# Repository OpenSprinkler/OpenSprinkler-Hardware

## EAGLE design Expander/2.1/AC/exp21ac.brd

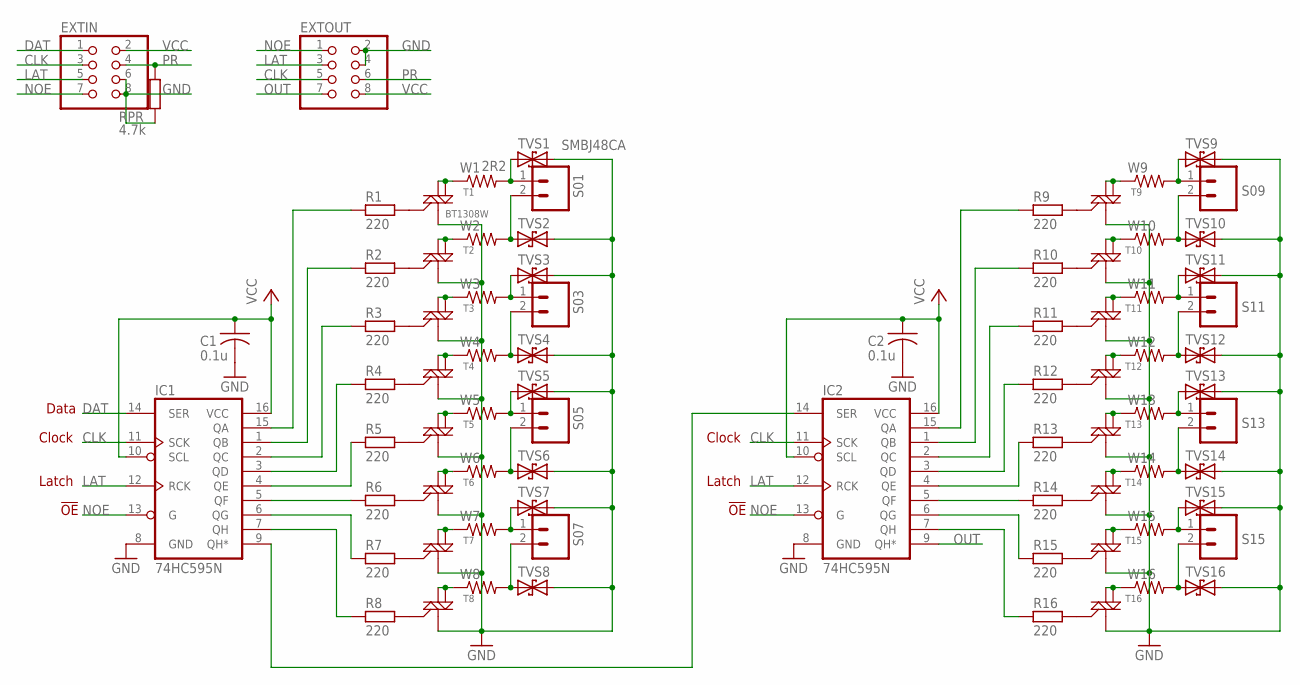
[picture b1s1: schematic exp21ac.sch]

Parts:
C1, C2: 0.1u; C0603K
EXTIN: PINHD-2X4/90; 2X04/90
EXTOUT: PINHD-2X4/90; 2X04/90
IC1, IC2: 74HC595N; SO16
R1, R2, R3, R4, R5, R6, R7, R8, R9, R10, R11, R12, R13, R14, R15, R16: 220; R0603
RPR: 4.7k; R0603
S01, S03, S05, S07, S09, S11, S13, S15: M025MM-X; SCREWTERMINAL-5MM-2-X
T1: BT1308W; SOT223
T2, T3, T4, T5, T6, T7, T8: MAC97SOT223; SOT223
T9, T10, T11, T12, T13, T14, T15, T16: MAC97; SOT223
TVS1: SMBJ48CA; SMB
TVS2, TVS3, TVS4, TVS5, TVS6, TVS7, TVS8, TVS9, TVS10, TVS11, TVS12, TVS13, TVS14, TVS15, TVS16: TVSSMB; SMB
W1: 2R2; R2512
W2, W3, W4, W5, W6, W7, W8, W9, W10, W11, W12, W13, W14, W15, W16: R-US_R2512; R2512

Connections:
CLK: EXTIN.3, EXTOUT.5, IC1.11 (SCK), IC2.11 (SCK)
DAT: EXTIN.1, IC1.14 (SER)
GND: C1.2, C2.2, EXTIN.6, EXTIN.8, EXTOUT.2, EXTOUT.4, IC1.8 (GND), IC2.8 (GND), RPR.1, T1.1 (M1), T2.1 (M1), T3.1 (M1), T4.1 (M1), T5.1 (M1), T6.1 (M1), T7.1 (M1), T8.1 (M1), T9.1 (M1), T10.1 (M1), T11.1 (M1), T12.1 (M1), T13.1 (M1), T14.1 (M1), T15.1 (M1), T16.1 (M1), TVS1.C (2), TVS2.C (2), TVS3.C (2), TVS4.C (2), TVS5.C (2), TVS6.C (2), TVS7.C (2), TVS8.C (2), TVS9.C (2), TVS10.C (2), TVS11.C (2), TVS12.C (2), TVS13.C (2), TVS14.C (2), TVS15.C (2), TVS16.C (2)
LAT: EXTIN.5, EXTOUT.3, IC1.12 (RCK), IC2.12 (RCK)
unnamed: S01.1, TVS1.A (1), W1.2
unnamed: S03.1, TVS3.A (1), W3.2
unnamed: S05.1, TVS5.A (1), W5.2
unnamed: IC1.5 (QF), R6.2
unnamed: IC1.6 (QG), R7.2
unnamed: S07.1, TVS7.A (1), W7.2
unnamed: IC1.7 (QH), R8.2
unnamed: R1.1, T1.3 (G)
unnamed: R2.1, T2.3 (G)
unnamed: IC1.4 (QE), R5.2
unnamed: IC1.3 (QD), R4.2
unnamed: IC1.2 (QC), R3.2
unnamed: IC1.1 (QB), R2.2
unnamed: IC1.15 (QA), R1.2
unnamed: R3.1, T3.3 (G)
unnamed: R4.1, T4.3 (G)
unnamed: S01.2, TVS2.A (1), W2.2
unnamed: R5.1, T5.3 (G)
unnamed: R6.1, T6.3 (G)
unnamed: S03.2, TVS4.A (1), W4.2
unnamed: R7.1, T7.3 (G)
unnamed: R8.1, T8.3 (G)
unnamed: S05.2, TVS6.A (1), W6.2
unnamed: IC2.5 (QF), R14.2
unnamed: S07.2, TVS8.A (1), W8.2
unnamed: IC2.6 (QG), R15.2
unnamed: IC2.7 (QH), R16.2
unnamed: IC2.4 (QE), R13.2
unnamed: IC2.3 (QD), R12.2
unnamed: IC2.2 (QC), R11.2
unnamed: IC2.1 (QB), R10.2
unnamed: IC2.15 (QA), R9.2
unnamed: S09.2, TVS10.A (1), W10.2
unnamed: S11.2, TVS12.A (1), W12.2
unnamed: S13.2, TVS14.A (1), W14.2
unnamed: S15.2, TVS16.A (1), W16.2
unnamed: S09.1, TVS9.A (1), W9.2
unnamed: S11.1, TVS11.A (1), W11.2
unnamed: S13.1, TVS13.A (1), W13.2
unnamed: S15.1, TVS15.A (1), W15.2
unnamed: R9.1, T9.3 (G)
unnamed: R10.1, T10.3 (G)
unnamed: R11.1, T11.3 (G)
unnamed: R12.1, T12.3 (G)
unnamed: R13.1, T13.3 (G)
unnamed: R14.1, T14.3 (G)
unnamed: R15.1, T15.3 (G)
unnamed: R16.1, T16.3 (G)
unnamed: IC1.9 (QH*), IC2.14 (SER)
unnamed: T1.2 (M2), T1.4 (M2-4), W1.1
unnamed: T2.2 (M2), T2.4 (M2-4), W2.1
unnamed: T3.2 (M2), T3.4 (M2-4), W3.1
unnamed: T4.2 (M2), T4.4 (M2-4), W4.1
unnamed: T5.2 (M2), T5.4 (M2-4), W5.1
unnamed: T6.2 (M2), T6.4 (M2-4), W6.1
unnamed: T7.2 (M2), T7.4 (M2-4), W7.1
unnamed: T8.2 (M2), T8.4 (M2-4), W8.1
unnamed: T9.2 (M2), T9.4 (M2-4), W9.1
unnamed: T10.2 (M2), T10.4 (M2-4), W10.1
unnamed: T11.2 (M2), T11.4 (M2-4), W11.1
unnamed: T12.2 (M2), T12.4 (M2-4), W12.1
unnamed: T13.2 (M2), T13.4 (M2-4), W13.1
unnamed: T14.2 (M2), T14.4 (M2-4), W14.1
unnamed: T15.2 (M2), T15.4 (M2-4), W15.1
unnamed: T16.2 (M2), T16.4 (M2-4), W16.1
NOE: EXTIN.7, EXTOUT.1, IC1.13 (G), IC2.13 (G)
OUT: EXTOUT.7, IC2.9 (QH*)
PR: EXTIN.4, EXTOUT.6, RPR.2
VCC: C1.1, C2.1, EXTIN.2, EXTOUT.8, IC1.10 (SCL), IC1.16 (VCC), IC2.10 (SCL), IC2.16 (VCC)

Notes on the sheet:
Data
Clock
Latch
!OE

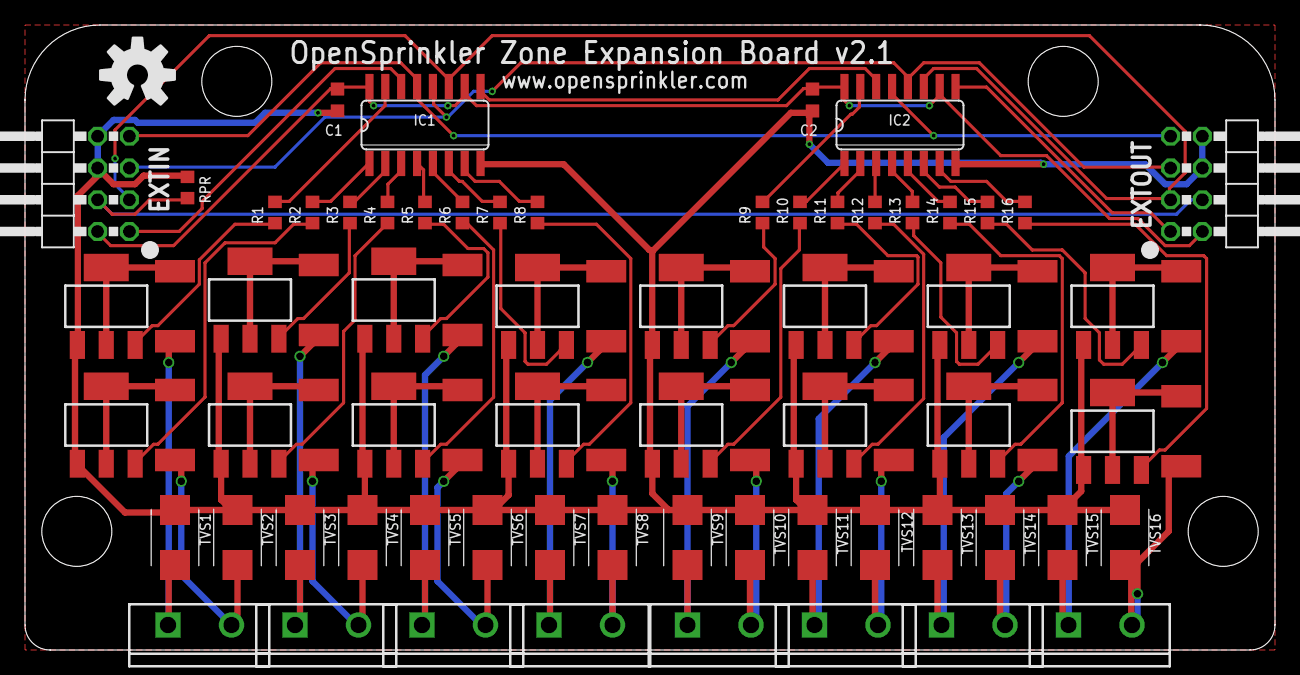
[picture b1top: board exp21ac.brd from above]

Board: 2 copper layers, 100.0 x 50.0 mm, 79 parts (0 on the bottom side), 73 nets.

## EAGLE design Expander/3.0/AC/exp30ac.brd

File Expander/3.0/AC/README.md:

- Original expander 3.0 uses PCF8575 16-channel IO expander. Due to the weak source current, PNP transistors are used per channel to provide higher source current needed to drive triac.

- Expander 3.0 revision 1 uses PCA9555 16-channel IO expander, which provides higher source current and therefore eliminates the need of PNP transistors.

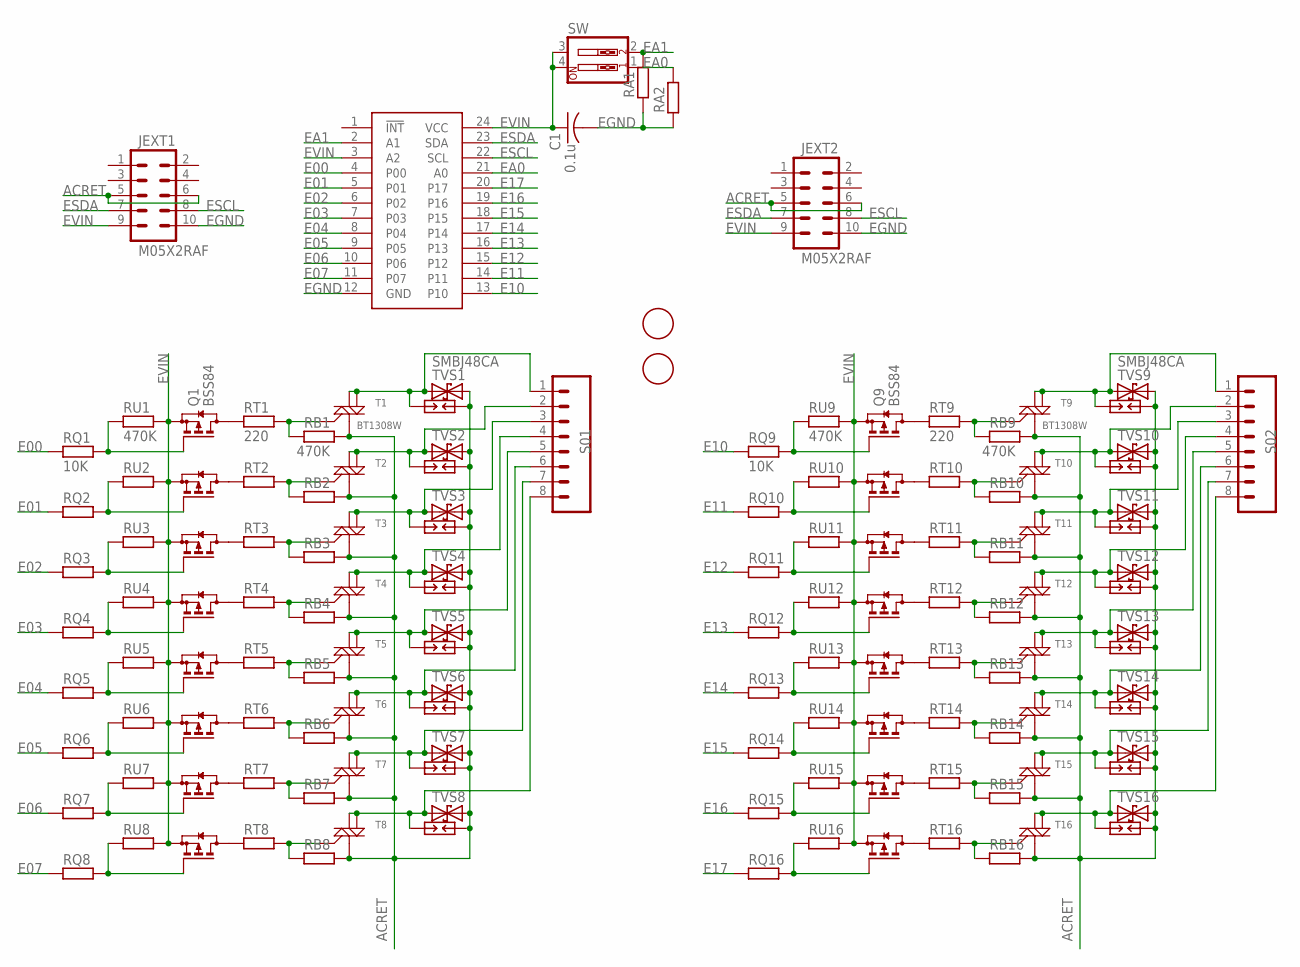
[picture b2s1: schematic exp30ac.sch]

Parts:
C1: 0.1u; C0603
JEXT1, JEXT2: M05X2RAF; 2X5-RAF
PCF8575: PCF8575; SSOP24
Q1, Q2, Q3, Q4, Q5, Q6, Q7, Q8, Q9, Q10, Q11, Q12, Q13, Q14, Q15, Q16: BSS84; SOT23
RA1, RA2: 10K; R0603
RB1, RB2, RB3, RB4, RB5, RB6, RB7, RB8, RB9, RB10, RB11, RB12, RB13, RB14, RB15, RB16: 470K; R0603
RQ1, RQ2, RQ3, RQ4, RQ5, RQ6, RQ7, RQ8, RQ9, RQ10, RQ11, RQ12, RQ13, RQ14, RQ15, RQ16: 10K; R0603
RT1, RT2, RT3, RT4, RT5, RT6, RT7, RT8, RT9, RT10, RT11, RT12, RT13, RT14, RT15, RT16: 220; R0603
RU1, RU2, RU3, RU4, RU5, RU6, RU7, RU8, RU9, RU10, RU11, RU12, RU13, RU14, RU15, RU16: 470K; R0603
S01, S02: M085MM-8; SCREWTERMINAL-5MM-8
SP1, SP2, SP3, SP4, SP5, SP6, SP7, SP8, SP9, SP10, SP11, SP12, SP13, SP14, SP15, SP16: PCB-SGAP
SW: SW_DIP-2; DIPSWITCH-02
T1, T9: BT1308W; SOT223
T2, T3, T4, T5, T6, T7, T8, T10, T11, T12, T13, T14, T15, T16: MAC97SOT223; SOT223
TVS1, TVS9: SMBJ48CA; SMB
TVS2, TVS3, TVS4, TVS5, TVS6, TVS7, TVS8, TVS10, TVS11, TVS12, TVS13, TVS14, TVS15, TVS16: TVSSMB; SMB
U$1, U$2: FIDUCIAL; FIDUCIAL_1MM

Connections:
ACRET: JEXT1.5, JEXT1.6, JEXT2.5, JEXT2.6, RB1.1, RB2.1, RB3.1, RB4.1, RB5.1, RB6.1, RB7.1, RB8.1, RB9.1, RB10.1, RB11.1, RB12.1, RB13.1, RB14.1, RB15.1, RB16.1, SP1.1, SP2.1, SP3.1, SP4.1, SP5.1, SP6.1, SP7.1, SP8.1, SP9.1, SP10.1, SP11.1, SP12.1, SP13.1, SP14.1, SP15.1, SP16.1, T1.1 (M1), T2.1 (M1), T3.1 (M1), T4.1 (M1), T5.1 (M1), T6.1 (M1), T7.1 (M1), T8.1 (M1), T9.1 (M1), T10.1 (M1), T11.1 (M1), T12.1 (M1), T13.1 (M1), T14.1 (M1), T15.1 (M1), T16.1 (M1), TVS1.C, TVS2.C, TVS3.C, TVS4.C, TVS5.C, TVS6.C, TVS7.C, TVS8.C, TVS9.C, TVS10.C, TVS11.C, TVS12.C, TVS13.C, TVS14.C, TVS15.C, TVS16.C
E00: PCF8575.4 (P00), RQ1.2
E01: PCF8575.5 (P01), RQ2.2
E02: PCF8575.6 (P02), RQ3.2
E03: PCF8575.7 (P03), RQ4.2
E04: PCF8575.8 (P04), RQ5.2
E05: PCF8575.9 (P05), RQ6.2
E06: PCF8575.10 (P06), RQ7.2
E07: PCF8575.11 (P07), RQ8.2
E10: PCF8575.13 (P10), RQ9.2
E11: PCF8575.14 (P11), RQ10.2
E12: PCF8575.15 (P12), RQ11.2
E13: PCF8575.16 (P13), RQ12.2
E14: PCF8575.17 (P14), RQ13.2
E15: PCF8575.18 (P15), RQ14.2
E16: PCF8575.19 (P16), RQ15.2
E17: PCF8575.20 (P17), RQ16.2
EA0: PCF8575.21 (A0), RA2.1, SW.1
EA1: PCF8575.2 (A1), RA1.1, SW.2
EGND: C1.2, JEXT1.10, JEXT2.10, PCF8575.12 (GND), RA1.2, RA2.2
ESCL: JEXT1.8, JEXT2.8, PCF8575.22 (SCL)
ESDA: JEXT1.7, JEXT2.7, PCF8575.23 (SDA)
EVIN: C1.1, JEXT1.9, JEXT2.9, PCF8575.3 (A2), PCF8575.24 (VCC), Q1.2 (S), Q2.2 (S), Q3.2 (S), Q4.2 (S), Q5.2 (S), Q6.2 (S), Q7.2 (S), Q8.2 (S), Q9.2 (S), Q10.2 (S), Q11.2 (S), Q12.2 (S), Q13.2 (S), Q14.2 (S), Q15.2 (S), Q16.2 (S), RU1.1, RU2.1, RU3.1, RU4.1, RU5.1, RU6.1, RU7.1, RU8.1, RU9.1, RU10.1, RU11.1, RU12.1, RU13.1, RU14.1, RU15.1, RU16.1, SW.3, SW.4
unnamed: RB9.2, RT9.1, T9.3 (G)
unnamed: Q1.3 (D), RT1.2
unnamed: Q2.3 (D), RT2.2
unnamed: Q3.3 (D), RT3.2
unnamed: Q4.3 (D), RT4.2
unnamed: Q5.3 (D), RT5.2
unnamed: Q6.3 (D), RT6.2
unnamed: RB1.2, RT1.1, T1.3 (G)
unnamed: RB2.2, RT2.1, T2.3 (G)
unnamed: Q7.3 (D), RT7.2
unnamed: Q8.3 (D), RT8.2
unnamed: Q1.1 (G), RQ1.1, RU1.2
unnamed: Q2.1 (G), RQ2.1, RU2.2
unnamed: Q3.1 (G), RQ3.1, RU3.2
unnamed: RB3.2, RT3.1, T3.3 (G)
unnamed: RB4.2, RT4.1, T4.3 (G)
unnamed: RB10.2, RT10.1, T10.3 (G)
unnamed: RB5.2, RT5.1, T5.3 (G)
unnamed: RB6.2, RT6.1, T6.3 (G)
unnamed: Q4.1 (G), RQ4.1, RU4.2
unnamed: RB7.2, RT7.1, T7.3 (G)
unnamed: RB8.2, RT8.1, T8.3 (G)
unnamed: Q5.1 (G), RQ5.1, RU5.2
unnamed: RB11.2, RT11.1, T11.3 (G)
unnamed: Q6.1 (G), RQ6.1, RU6.2
unnamed: RB12.2, RT12.1, T12.3 (G)
unnamed: RB13.2, RT13.1, T13.3 (G)
unnamed: RB14.2, RT14.1, T14.3 (G)
unnamed: RB15.2, RT15.1, T15.3 (G)
unnamed: RB16.2, RT16.1, T16.3 (G)
unnamed: Q7.1 (G), RQ7.1, RU7.2
unnamed: Q8.1 (G), RQ8.1, RU8.2
unnamed: S02.1, SP9.2, T9.2 (M2), T9.4 (M2-4), TVS9.A
unnamed: S02.2, SP10.2, T10.2 (M2), T10.4 (M2-4), TVS10.A
unnamed: S02.3, SP11.2, T11.2 (M2), T11.4 (M2-4), TVS11.A
unnamed: S02.4, SP12.2, T12.2 (M2), T12.4 (M2-4), TVS12.A
unnamed: S02.5, SP13.2, T13.2 (M2), T13.4 (M2-4), TVS13.A
unnamed: S02.6, SP14.2, T14.2 (M2), T14.4 (M2-4), TVS14.A
unnamed: S02.7, SP15.2, T15.2 (M2), T15.4 (M2-4), TVS15.A
unnamed: S02.8, SP16.2, T16.2 (M2), T16.4 (M2-4), TVS16.A
unnamed: Q9.3 (D), RT9.2
unnamed: Q10.3 (D), RT10.2
unnamed: Q11.3 (D), RT11.2
unnamed: Q12.3 (D), RT12.2
unnamed: Q13.3 (D), RT13.2
unnamed: Q14.3 (D), RT14.2
unnamed: Q15.3 (D), RT15.2
unnamed: Q16.3 (D), RT16.2
unnamed: Q9.1 (G), RQ9.1, RU9.2
unnamed: S01.1, SP1.2, T1.2 (M2), T1.4 (M2-4), TVS1.A
unnamed: S01.2, SP2.2, T2.2 (M2), T2.4 (M2-4), TVS2.A
unnamed: S01.3, SP3.2, T3.2 (M2), T3.4 (M2-4), TVS3.A
unnamed: S01.4, SP4.2, T4.2 (M2), T4.4 (M2-4), TVS4.A
unnamed: S01.5, SP5.2, T5.2 (M2), T5.4 (M2-4), TVS5.A
unnamed: S01.6, SP6.2, T6.2 (M2), T6.4 (M2-4), TVS6.A
unnamed: S01.7, SP7.2, T7.2 (M2), T7.4 (M2-4), TVS7.A
unnamed: S01.8, SP8.2, T8.2 (M2), T8.4 (M2-4), TVS8.A
unnamed: Q10.1 (G), RQ10.1, RU10.2
unnamed: Q11.1 (G), RQ11.1, RU11.2
unnamed: Q12.1 (G), RQ12.1, RU12.2
unnamed: Q13.1 (G), RQ13.1, RU13.2
unnamed: Q14.1 (G), RQ14.1, RU14.2
unnamed: Q15.1 (G), RQ15.1, RU15.2
unnamed: Q16.1 (G), RQ16.1, RU16.2

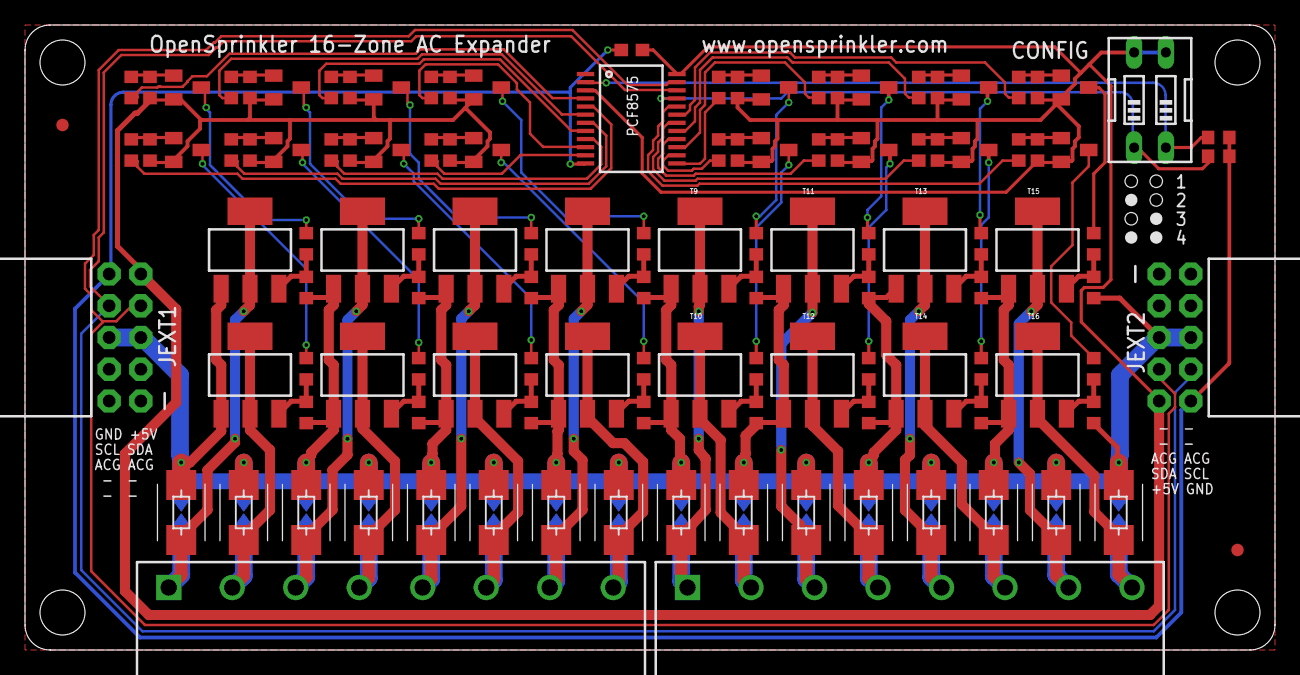
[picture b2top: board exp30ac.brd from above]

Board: 2 copper layers, 100.0 x 50.0 mm, 139 parts (0 on the bottom side), 87 nets.

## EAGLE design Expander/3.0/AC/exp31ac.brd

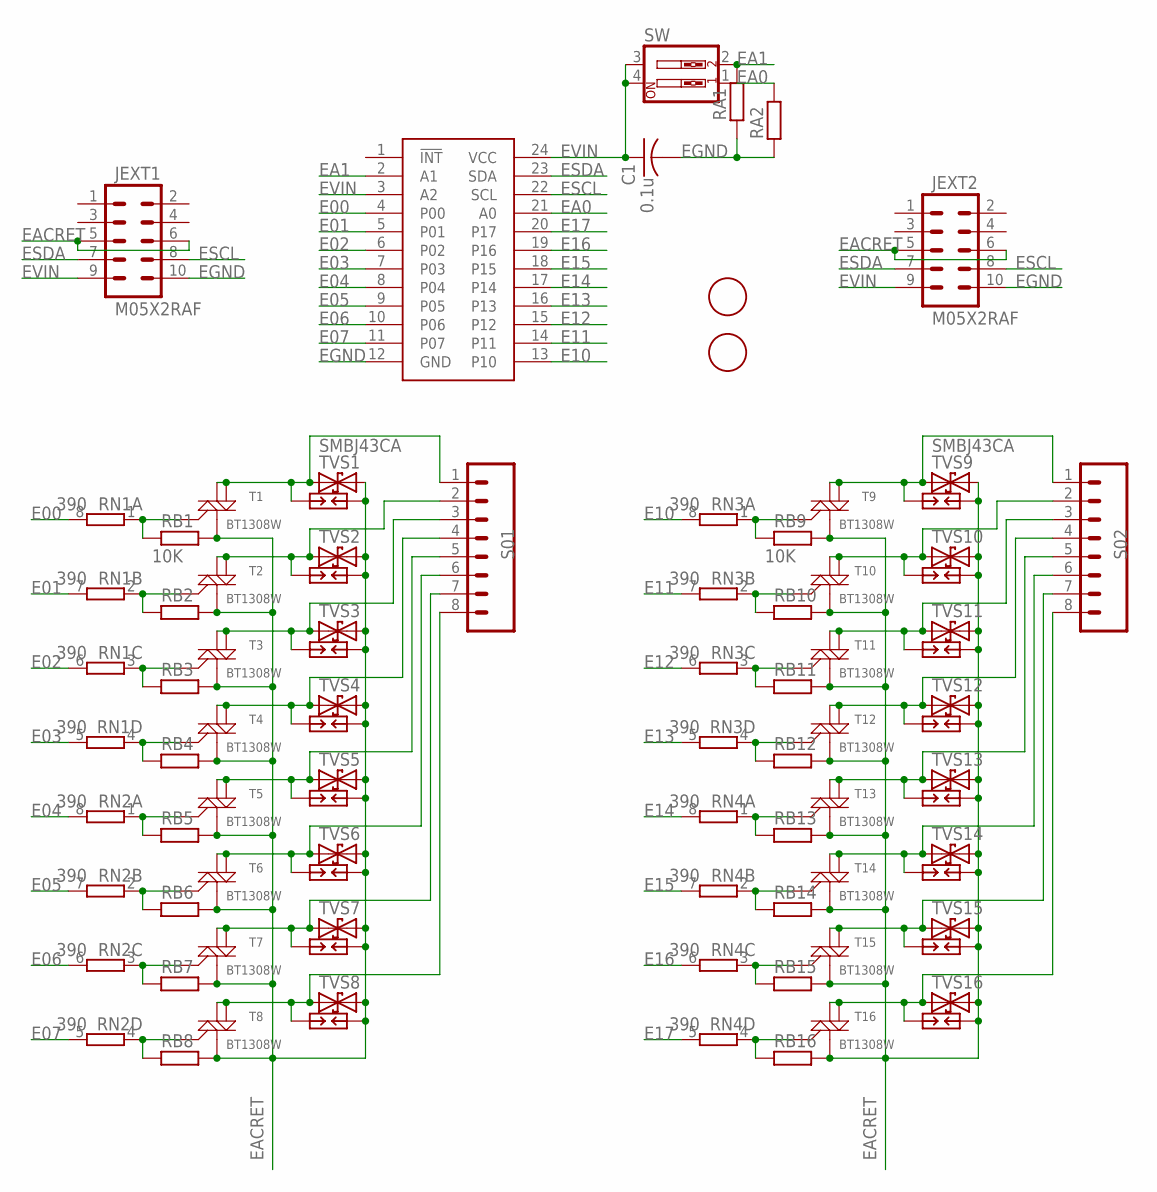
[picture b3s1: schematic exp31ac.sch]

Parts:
C1: 0.1u; C0603
JEXT1, JEXT2: M05X2RAF; 2X5-RAF
PCA9555: PCA9555PW; TSSOP24
RA1, RA2: 10K; R0603
RB1, RB2, RB3, RB4, RB5, RB6, RB7, RB8, RB9, RB10, RB11, RB12, RB13, RB14, RB15, RB16: 10K; R0603
RN1, RN2, RN3, RN4: 390; EXB38V
S01, S02: M085MM-8; SCREWTERMINAL-5MM-8
SP1, SP2, SP3, SP4, SP5, SP6, SP7, SP8, SP9, SP10, SP11, SP12, SP13, SP14, SP15, SP16: PCB-SGAP
SW: SW_DIP-2; DIPSWITCH-02
T1, T2, T3, T4, T5, T6, T7, T8, T9, T10, T11, T12, T13, T14, T15, T16: BT1308W; SOT223
TVS1, TVS2, TVS3, TVS4, TVS5, TVS6, TVS7, TVS8, TVS9, TVS10, TVS11, TVS12, TVS13, TVS14, TVS15, TVS16: SMBJ43CA; SMB
U$1, U$2: FIDUCIAL; FIDUCIAL_1MM

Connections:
E00: PCA9555.4 (P00), RN1.8 (2)
E01: PCA9555.5 (P01), RN1.7 (2)
E02: PCA9555.6 (P02), RN1.6 (2)
E03: PCA9555.7 (P03), RN1.5 (2)
E04: PCA9555.8 (P04), RN2.8 (2)
E05: PCA9555.9 (P05), RN2.7 (2)
E06: PCA9555.10 (P06), RN2.6 (2)
E07: PCA9555.11 (P07), RN2.5 (2)
E10: PCA9555.13 (P10), RN3.8 (2)
E11: PCA9555.14 (P11), RN3.7 (2)
E12: PCA9555.15 (P12), RN3.6 (2)
E13: PCA9555.16 (P13), RN3.5 (2)
E14: PCA9555.17 (P14), RN4.8 (2)
E15: PCA9555.18 (P15), RN4.7 (2)
E16: PCA9555.19 (P16), RN4.6 (2)
E17: PCA9555.20 (P17), RN4.5 (2)
EA0: PCA9555.21 (A0), RA2.1, SW.1
EA1: PCA9555.2 (A1), RA1.1, SW.2
EACRET: JEXT1.5, JEXT1.6, JEXT2.5, JEXT2.6, RB1.1, RB2.1, RB3.1, RB4.1, RB5.1, RB6.1, RB7.1, RB8.1, RB9.1, RB10.1, RB11.1, RB12.1, RB13.1, RB14.1, RB15.1, RB16.1, SP1.1, SP2.1, SP3.1, SP4.1, SP5.1, SP6.1, SP7.1, SP8.1, SP9.1, SP10.1, SP11.1, SP12.1, SP13.1, SP14.1, SP15.1, SP16.1, T1.1 (M1), T2.1 (M1), T3.1 (M1), T4.1 (M1), T5.1 (M1), T6.1 (M1), T7.1 (M1), T8.1 (M1), T9.1 (M1), T10.1 (M1), T11.1 (M1), T12.1 (M1), T13.1 (M1), T14.1 (M1), T15.1 (M1), T16.1 (M1), TVS1.C, TVS2.C, TVS3.C, TVS4.C, TVS5.C, TVS6.C, TVS7.C, TVS8.C, TVS9.C, TVS10.C, TVS11.C, TVS12.C, TVS13.C, TVS14.C, TVS15.C, TVS16.C
EGND: C1.2, JEXT1.10, JEXT2.10, PCA9555.12 (GND), RA1.2, RA2.2
ESCL: JEXT1.8, JEXT2.8, PCA9555.22 (SCL)
ESDA: JEXT1.7, JEXT2.7, PCA9555.23 (SDA)
EVIN: C1.1, JEXT1.9, JEXT2.9, PCA9555.3 (A2), PCA9555.24 (VCC), SW.3, SW.4
unnamed: RB9.2, RN3.1, T9.3 (G)
unnamed: RB1.2, RN1.1, T1.3 (G)
unnamed: RB2.2, RN1.2 (1), T2.3 (G)
unnamed: RB3.2, RN1.3 (1), T3.3 (G)
unnamed: RB4.2, RN1.4 (1), T4.3 (G)
unnamed: RB10.2, RN3.2 (1), T10.3 (G)
unnamed: RB5.2, RN2.1, T5.3 (G)
unnamed: RB6.2, RN2.2 (1), T6.3 (G)
unnamed: RB7.2, RN2.3 (1), T7.3 (G)
unnamed: RB8.2, RN2.4 (1), T8.3 (G)
unnamed: RB11.2, RN3.3 (1), T11.3 (G)
unnamed: RB12.2, RN3.4 (1), T12.3 (G)
unnamed: RB13.2, RN4.1, T13.3 (G)
unnamed: RB14.2, RN4.2 (1), T14.3 (G)
unnamed: RB15.2, RN4.3 (1), T15.3 (G)
unnamed: RB16.2, RN4.4 (1), T16.3 (G)
unnamed: S02.1, SP9.2, T9.2 (M2), T9.4 (M2-4), TVS9.A
unnamed: S02.2, SP10.2, T10.2 (M2), T10.4 (M2-4), TVS10.A
unnamed: S02.3, SP11.2, T11.2 (M2), T11.4 (M2-4), TVS11.A
unnamed: S02.4, SP12.2, T12.2 (M2), T12.4 (M2-4), TVS12.A
unnamed: S02.5, SP13.2, T13.2 (M2), T13.4 (M2-4), TVS13.A
unnamed: S02.6, SP14.2, T14.2 (M2), T14.4 (M2-4), TVS14.A
unnamed: S02.7, SP15.2, T15.2 (M2), T15.4 (M2-4), TVS15.A
unnamed: S02.8, SP16.2, T16.2 (M2), T16.4 (M2-4), TVS16.A
unnamed: S01.1, SP1.2, T1.2 (M2), T1.4 (M2-4), TVS1.A
unnamed: S01.2, SP2.2, T2.2 (M2), T2.4 (M2-4), TVS2.A
unnamed: S01.3, SP3.2, T3.2 (M2), T3.4 (M2-4), TVS3.A
unnamed: S01.4, SP4.2, T4.2 (M2), T4.4 (M2-4), TVS4.A
unnamed: S01.5, SP5.2, T5.2 (M2), T5.4 (M2-4), TVS5.A
unnamed: S01.6, SP6.2, T6.2 (M2), T6.4 (M2-4), TVS6.A
unnamed: S01.7, SP7.2, T7.2 (M2), T7.4 (M2-4), TVS7.A
unnamed: S01.8, SP8.2, T8.2 (M2), T8.4 (M2-4), TVS8.A

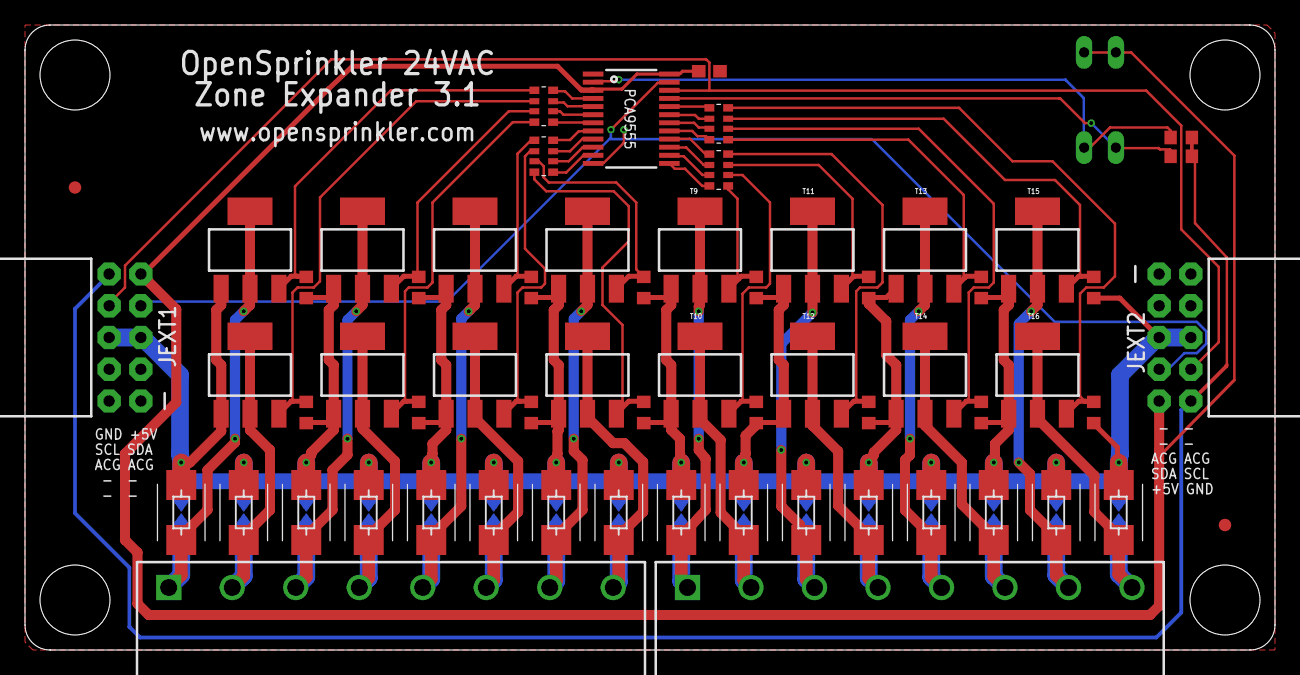
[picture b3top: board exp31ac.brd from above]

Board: 2 copper layers, 100.0 x 50.0 mm, 79 parts (1 on the bottom side), 55 nets.

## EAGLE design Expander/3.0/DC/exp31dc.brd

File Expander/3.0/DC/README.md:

- Original expander 3.0 uses PCF8575 16-channel IO expander.

- Expander 3.0 revision 1 uses PCA9555 16-channel IO expander.

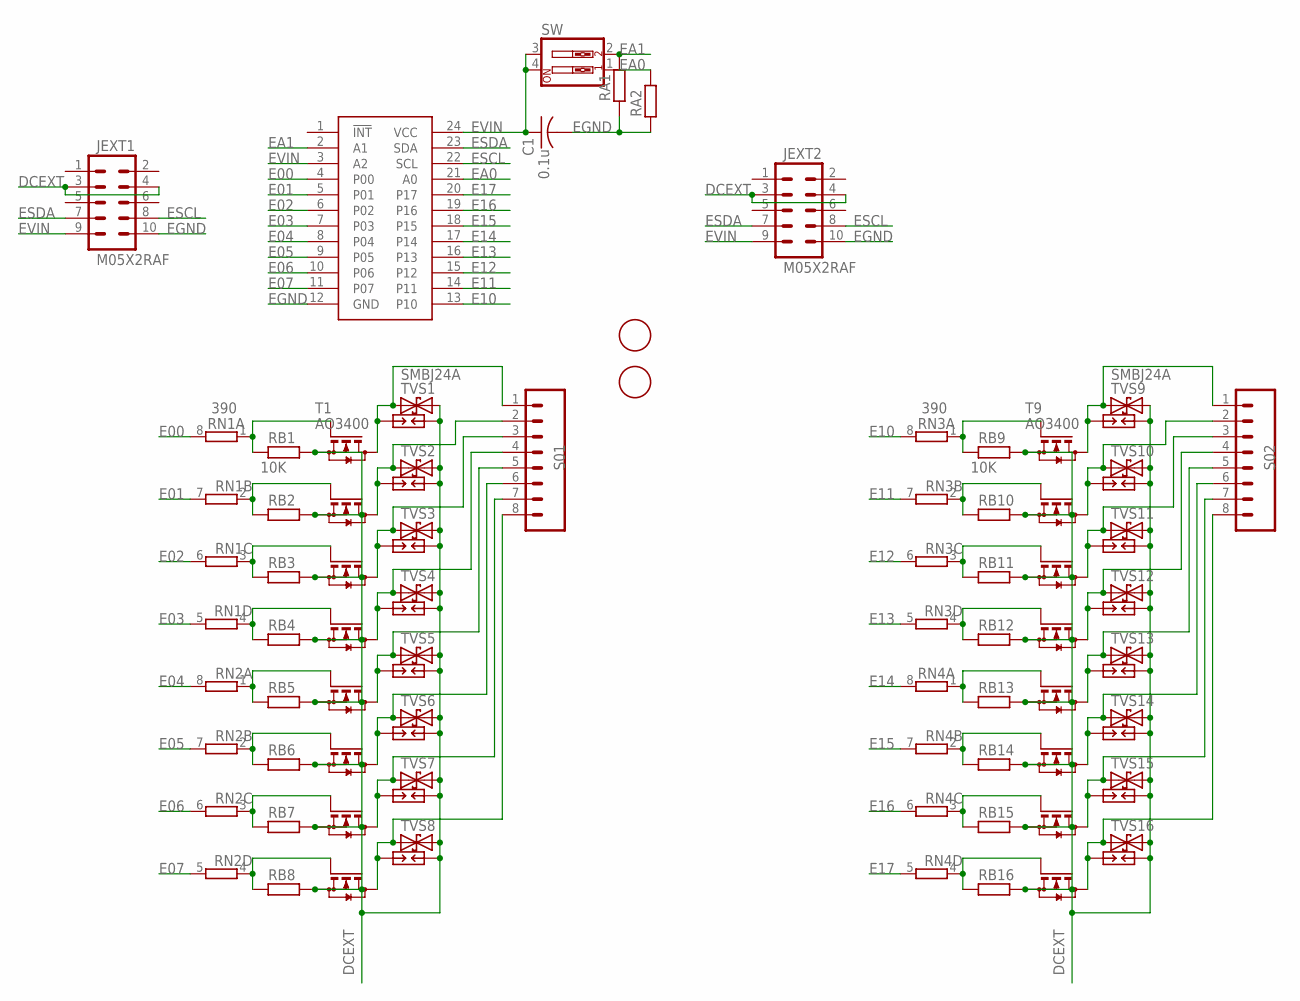
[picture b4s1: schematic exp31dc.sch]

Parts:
C1: 0.1u; C0603
JEXT1, JEXT2: M05X2RAF; 2X5-RAF
PCA9555: PCA9555; TSSOP24
RA1, RA2: 10K; R0603
RB1, RB2, RB3, RB4, RB5, RB6, RB7, RB8, RB9, RB10, RB11, RB12, RB13, RB14, RB15, RB16: 10K; R0603
RN1, RN2, RN3, RN4: 390; EXB38V
S01, S02: M085MM-8; SCREWTERMINAL-5MM-8
SP1, SP2, SP3, SP4, SP5, SP6, SP7, SP8, SP9, SP10, SP11, SP12, SP13, SP14, SP15, SP16: PCB-SGAP
SW: SW_DIP-2; DIPSWITCH-02
T1, T2, T3, T4, T5, T6, T7, T8, T9, T10, T11, T12, T13, T14, T15, T16: AO3400; SOT23
TVS1, TVS2, TVS3, TVS4, TVS5, TVS6, TVS7, TVS8, TVS9, TVS10, TVS11, TVS12, TVS13, TVS14, TVS15, TVS16: SMBJ24A; SMB
U$1, U$2: FIDUCIAL; FIDUCIAL_1MM

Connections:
DCEXT: JEXT1.3, JEXT1.4, JEXT2.3, JEXT2.4, RB1.1, RB2.1, RB3.1, RB4.1, RB5.1, RB6.1, RB7.1, RB8.1, RB9.1, RB10.1, RB11.1, RB12.1, RB13.1, RB14.1, RB15.1, RB16.1, SP1.1, SP2.1, SP3.1, SP4.1, SP5.1, SP6.1, SP7.1, SP8.1, SP9.1, SP10.1, SP11.1, SP12.1, SP13.1, SP14.1, SP15.1, SP16.1, T1.2 (S), T2.2 (S), T3.2 (S), T4.2 (S), T5.2 (S), T6.2 (S), T7.2 (S), T8.2 (S), T9.2 (S), T10.2 (S), T11.2 (S), T12.2 (S), T13.2 (S), T14.2 (S), T15.2 (S), T16.2 (S), TVS1.C, TVS2.C, TVS3.C, TVS4.C, TVS5.C, TVS6.C, TVS7.C, TVS8.C, TVS9.C, TVS10.C, TVS11.C, TVS12.C, TVS13.C, TVS14.C, TVS15.C, TVS16.C
E00: PCA9555.4 (P00), RN1.8 (2)
E01: PCA9555.5 (P01), RN1.7 (2)
E02: PCA9555.6 (P02), RN1.6 (2)
E03: PCA9555.7 (P03), RN1.5 (2)
E04: PCA9555.8 (P04), RN2.8 (2)
E05: PCA9555.9 (P05), RN2.7 (2)
E06: PCA9555.10 (P06), RN2.6 (2)
E07: PCA9555.11 (P07), RN2.5 (2)
E10: PCA9555.13 (P10), RN3.8 (2)
E11: PCA9555.14 (P11), RN3.7 (2)
E12: PCA9555.15 (P12), RN3.6 (2)
E13: PCA9555.16 (P13), RN3.5 (2)
E14: PCA9555.17 (P14), RN4.8 (2)
E15: PCA9555.18 (P15), RN4.7 (2)
E16: PCA9555.19 (P16), RN4.6 (2)
E17: PCA9555.20 (P17), RN4.5 (2)
EA0: PCA9555.21 (A0), RA2.1, SW.1
EA1: PCA9555.2 (A1), RA1.1, SW.2
EGND: C1.2, JEXT1.10, JEXT2.10, PCA9555.12 (GND), RA1.2, RA2.2
ESCL: JEXT1.8, JEXT2.8, PCA9555.22 (SCL)
ESDA: JEXT1.7, JEXT2.7, PCA9555.23 (SDA)
EVIN: C1.1, JEXT1.9, JEXT2.9, PCA9555.3 (A2), PCA9555.24 (VCC), SW.3, SW.4
unnamed: RB9.2, RN3.1, T9.1 (G)
unnamed: RB4.2, RN1.4 (1), T4.1 (G)
unnamed: RB3.2, RN1.3 (1), T3.1 (G)
unnamed: RB1.2, RN1.1, T1.1 (G)
unnamed: RB2.2, RN1.2 (1), T2.1 (G)
unnamed: RB10.2, RN3.2 (1), T10.1 (G)
unnamed: RB5.2, RN2.1, T5.1 (G)
unnamed: RB6.2, RN2.2 (1), T6.1 (G)
unnamed: RB7.2, RN2.3 (1), T7.1 (G)
unnamed: RB8.2, RN2.4 (1), T8.1 (G)
unnamed: RB11.2, RN3.3 (1), T11.1 (G)
unnamed: RB12.2, RN3.4 (1), T12.1 (G)
unnamed: RB13.2, RN4.1, T13.1 (G)
unnamed: RB14.2, RN4.2 (1), T14.1 (G)
unnamed: RB15.2, RN4.3 (1), T15.1 (G)
unnamed: RB16.2, RN4.4 (1), T16.1 (G)
unnamed: S02.1, SP9.2, T9.3 (D), TVS9.A
unnamed: S02.2, SP10.2, T10.3 (D), TVS10.A
unnamed: S02.3, SP11.2, T11.3 (D), TVS11.A
unnamed: S02.4, SP12.2, T12.3 (D), TVS12.A
unnamed: S02.5, SP13.2, T13.3 (D), TVS13.A
unnamed: S02.6, SP14.2, T14.3 (D), TVS14.A
unnamed: S02.7, SP15.2, T15.3 (D), TVS15.A
unnamed: S02.8, SP16.2, T16.3 (D), TVS16.A
unnamed: S01.1, SP1.2, T1.3 (D), TVS1.A
unnamed: S01.2, SP2.2, T2.3 (D), TVS2.A
unnamed: S01.3, SP3.2, T3.3 (D), TVS3.A
unnamed: S01.4, SP4.2, T4.3 (D), TVS4.A
unnamed: S01.5, SP5.2, T5.3 (D), TVS5.A
unnamed: S01.6, SP6.2, T6.3 (D), TVS6.A
unnamed: S01.7, SP7.2, T7.3 (D), TVS7.A
unnamed: S01.8, SP8.2, T8.3 (D), TVS8.A

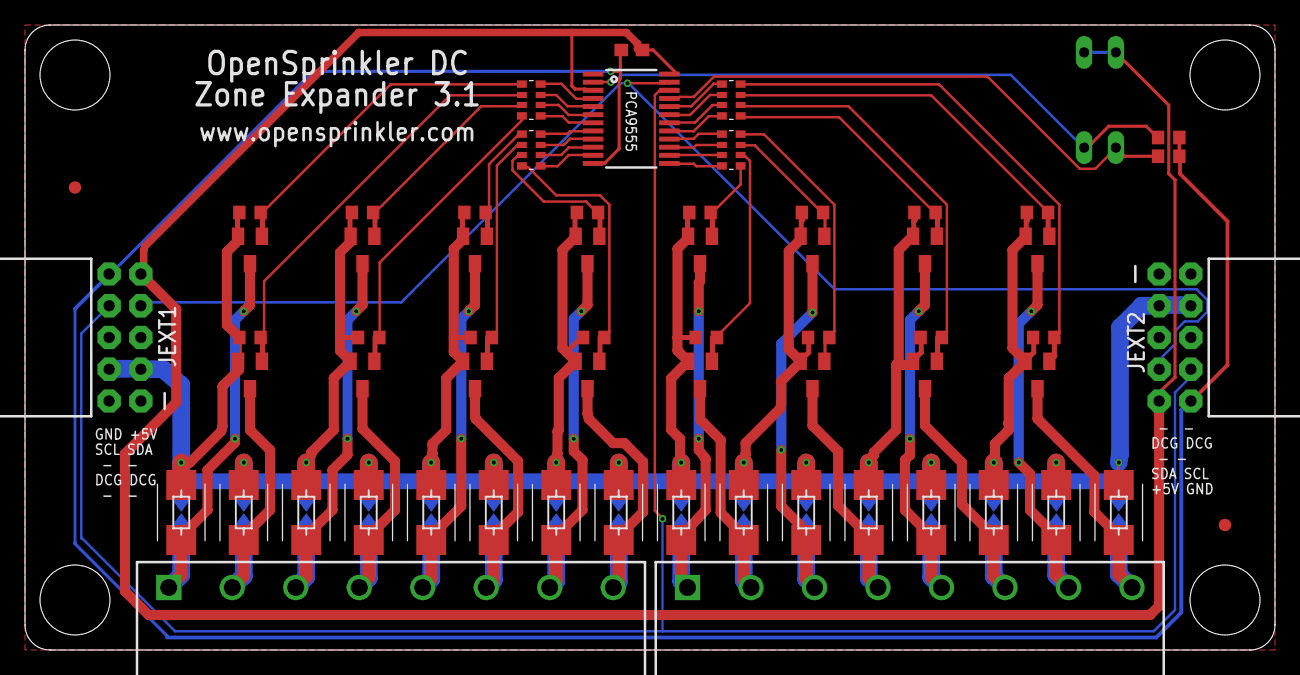
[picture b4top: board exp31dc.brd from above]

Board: 2 copper layers, 100.0 x 50.0 mm, 79 parts (1 on the bottom side), 55 nets.

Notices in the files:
parts and their libraries:
SparkFunNew: Licensing: CC v3.0 Share-Alike You are welcome to use this library for commercial purposes.
